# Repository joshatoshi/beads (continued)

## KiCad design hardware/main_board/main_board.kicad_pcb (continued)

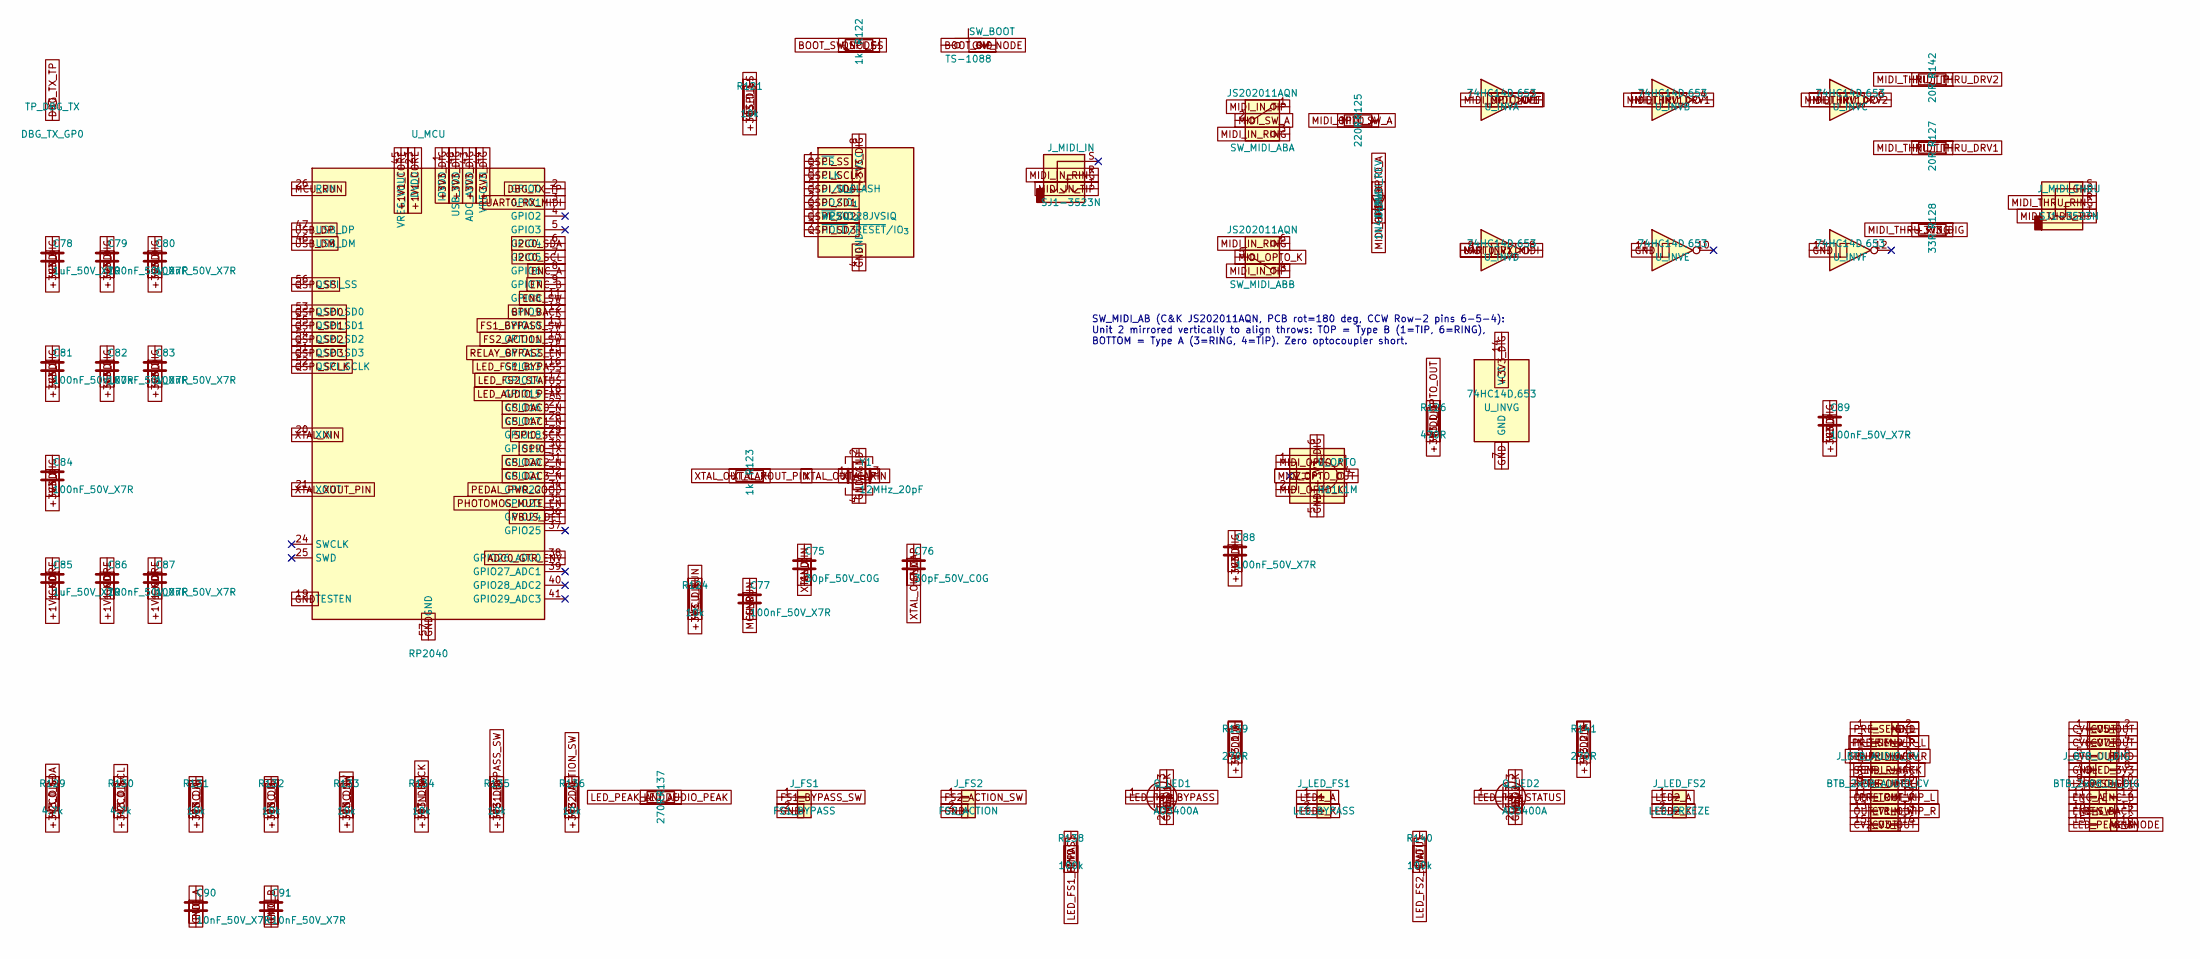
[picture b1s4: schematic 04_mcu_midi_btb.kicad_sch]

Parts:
C75, C76: 30pF_50V_C0G; C_0603_1608Metric
C77, C79, C80, C81, C82, C83, C84, C86, C87, C88, C89: 100nF_50V_X7R; C_0603_1608Metric
C78, C85: 1uF_50V_X7R; C_0805_2012Metric
C90, C91: 10nF_50V_X7R; C_0603_1608Metric
D_MIDI_REV: 1N4148W; D_SOD-123
J_BTB_AUDIO_CV: BTB_2x08_AUDIO_CV; PinHeader_2x08_P2.54mm_Vertical
J_BTB_UI_DIG: BTB_2x08_UI_DIG; PinHeader_2x08_P2.54mm_Vertical
J_FS1: FS1_BYPASS; PinHeader_1x02_P2.54mm_Vertical
J_FS2: FS2_ACTION; PinHeader_1x02_P2.54mm_Vertical
J_LED_FS1: LED_BYPASS; PinHeader_1x02_P2.54mm_Vertical
J_LED_FS2: LED_FREEZE; PinHeader_1x02_P2.54mm_Vertical
J_MIDI_IN: SJ1-3523N; Jack_3.5mm_CUI_SJ1-3523N_Clean
J_MIDI_THRU: SJ1-3523N; Jack_3.5mm_CUI_SJ1-3523N_Clean
Q_LED1, Q_LED2: AO3400A; SOT-23
R121, R124, R131, R132, R133, R134, R135, R136: 10k; R_0603_1608Metric
R122, R123: 1k; R_0603_1608Metric
R125: 220R; R_0603_1608Metric
R126: 470R; R_0603_1608Metric
R127, R142: 20R; R_0603_1608Metric
R128: 33R; R_0603_1608Metric
R129, R130: 4.7k; R_0603_1608Metric
R137, R139, R141: 270R; R_0603_1608Metric
R138, R140: 100k; R_0603_1608Metric
SW_BOOT: TS-1088; SW_Push_TS-1088_4.0x3.0mm
SW_MIDI_AB: JS202011AQN; SW_CK_JS202011AQN_DPDT_Angled
TP_DBG_TX: DBG_TX_GP0; TestPoint_Pad_D1.0mm
U_FLASH: W25Q128JVSIQ; SOIC-8_5.3x5.3mm_P1.27mm
U_INV: 74HC14D,653; SOIC-14_3.9x8.7mm_P1.27mm
U_MCU: RP2040; QFN-56-1EP_7x7mm_RP2040_SegPaste
U_OPTO: H11L1M; DIP-6_W7.62mm
Y1: 12MHz_20pF; Crystal_SMD_3225-4Pin_3.2x2.5mm

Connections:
+1V1_CORE: C85.1, C86.1, C87.1, U_MCU.23 (DVDD), U_MCU.45 (VREG_VOUT), U_MCU.50 (DVDD)
+3V3_DIG: C78.1, C79.1, C80.1, C81.1, C82.1, C83.1, C84.1, C88.1, C89.1, R121.1, R124.1, R126.1, R128.1, R129.1, R130.1, R131.1, R132.1, R133.1, R134.1, R135.1, R136.1, R139.1, R141.1, U_FLASH.8 (VCC), U_INV.14 (VCC), U_MCU.1 (IOVDD), U_MCU.10 (IOVDD), U_MCU.22 (IOVDD), U_MCU.33 (IOVDD), U_MCU.42 (IOVDD), U_MCU.43 (ADC_AVDD), U_MCU.44 (VREG_IN), U_MCU.48 (USB_VDD), U_MCU.49 (IOVDD), U_OPTO.6; also elsewhere on the board
ADC0_GTR_ENV: U_MCU.38 (GPIO26_ADC0); also elsewhere on the board
BOOT_SW_NODE: R122.2, SW_BOOT.1
BTN_BACK: J_BTB_UI_DIG.14, R134.2, U_MCU.12 (GPIO9)
CS_DAC0_N: U_MCU.27 (GPIO16); also elsewhere on the board
CS_DAC1_N: U_MCU.28 (GPIO17); also elsewhere on the board
CS_DAC2_N: U_MCU.31 (GPIO20); also elsewhere on the board
CS_DAC3_N: U_MCU.32 (GPIO21); also elsewhere on the board
CV1_OUT: J_BTB_AUDIO_CV.14; also elsewhere on the board
CV2_OUT: J_BTB_AUDIO_CV.15; also elsewhere on the board
CV3_OUT: J_BTB_AUDIO_CV.16; also elsewhere on the board
CV4_OUT: J_BTB_UI_DIG.1; also elsewhere on the board
CV5_OUT: J_BTB_UI_DIG.2; also elsewhere on the board
CV6_OUT: J_BTB_UI_DIG.3; also elsewhere on the board
CV7_OUT: J_BTB_UI_DIG.4; also elsewhere on the board
CV8_OUT: J_BTB_UI_DIG.5; also elsewhere on the board
DBG_TX_TP: TP_DBG_TX.1, U_MCU.2 (GPIO0)
ENC_A: C90.1, J_BTB_UI_DIG.11, R131.2, U_MCU.8 (GPIO6)
ENC_B: C91.1, J_BTB_UI_DIG.12, R132.2, U_MCU.9 (GPIO7)
ENC_SW: J_BTB_UI_DIG.13, R133.2, U_MCU.11 (GPIO8)
FS1_BYPASS_SW: J_FS1.1, R135.2, U_MCU.13 (GPIO10)
FS2_ACTION_SW: J_FS2.1, R136.2, U_MCU.14 (GPIO11)
GND: C75.2, C76.2, C77.2, C78.2, C79.2, C80.2, C81.2, C82.2, C83.2, C84.2, C85.2, C86.2, C87.2, C88.2, C89.2, C90.2, C91.2, J_BTB_AUDIO_CV.2, J_BTB_UI_DIG.6, J_BTB_UI_DIG.7, J_BTB_UI_DIG.16, J_FS1.2, J_FS2.2, J_MIDI_THRU.S, Q_LED1.2 (S), Q_LED2.2 (S), R138.2, R140.2, SW_BOOT.2, U_FLASH.4 (GND), U_INV.7 (GND), U_INV.11, U_INV.13, U_MCU.19 (TESTEN), U_MCU.57 (GND), U_OPTO.5, Y1.2, Y1.4; also elsewhere on the board
I2C0_SCL: J_BTB_UI_DIG.10, R130.2, U_MCU.7 (GPIO5)
I2C0_SDA: J_BTB_UI_DIG.9, R129.2, U_MCU.6 (GPIO4)
IN_TRIM_WIP_L: J_BTB_AUDIO_CV.3; also elsewhere on the board
IN_TRIM_WIP_R: J_BTB_AUDIO_CV.5; also elsewhere on the board
LED1_A: J_LED_FS1.1, R139.2
LED1_K: J_LED_FS1.2, Q_LED1.3 (D)
LED2_A: J_LED_FS2.1, R141.2
LED2_K: J_LED_FS2.2, Q_LED2.3 (D)
LED_AUDIO_PEAK: R137.1, U_MCU.18 (GPIO15)
LED_FS1_BYPASS: Q_LED1.1 (G), R138.1, U_MCU.16 (GPIO13)
LED_FS2_STATUS: Q_LED2.1 (G), R140.1, U_MCU.17 (GPIO14)
LED_PEAK_ANODE: J_BTB_UI_DIG.15, R137.2
MCU_RUN: C77.1, R124.2, U_MCU.26 (RUN)
MIDI_INV1: U_INV.2, U_INV.3, U_INV.5, U_INV.9
MIDI_IN_RING: J_MIDI_IN.R, SW_MIDI_AB.3 (C), SW_MIDI_AB.6 (C)
MIDI_IN_TIP: J_MIDI_IN.T, SW_MIDI_AB.1 (A), SW_MIDI_AB.4 (A)
MIDI_OPTO_A: D_MIDI_REV.1 (K), R125.2, U_OPTO.1
MIDI_OPTO_K: D_MIDI_REV.2 (A), SW_MIDI_AB.5 (B), U_OPTO.2
MIDI_OPTO_OUT: R126.2, U_INV.1, U_OPTO.4
MIDI_SW_A: R125.1, SW_MIDI_AB.2 (B)
MIDI_THRU_DRV1: R127.1, U_INV.4
MIDI_THRU_DRV2: R142.1, U_INV.6
MIDI_THRU_RING: J_MIDI_THRU.R, R128.2
MIDI_THRU_TIP: J_MIDI_THRU.T, R127.2, R142.2
OLED_3V3: J_BTB_UI_DIG.8; also elsewhere on the board
OUT_TRIM_WIP_L: J_BTB_AUDIO_CV.11; also elsewhere on the board
OUT_TRIM_WIP_R: J_BTB_AUDIO_CV.13; also elsewhere on the board
PEDAL_PWR_GOOD: U_MCU.34 (GPIO22); also elsewhere on the board
PHOTOMOS_MUTE_EN: U_MCU.35 (GPIO23); also elsewhere on the board
PRE_OUT_L: J_BTB_AUDIO_CV.10; also elsewhere on the board
PRE_OUT_R: J_BTB_AUDIO_CV.12; also elsewhere on the board
PRE_SEND_L: J_BTB_AUDIO_CV.1; also elsewhere on the board
PRE_SEND_R: J_BTB_AUDIO_CV.4; also elsewhere on the board
QSPI_SCLK: U_FLASH.6 (CLK), U_MCU.52 (QSPI_SCLK)
QSPI_SD0: U_FLASH.5 (DI/IO_{0}), U_MCU.53 (QSPI_SD0)
QSPI_SD1: U_FLASH.2 (DO/IO_{1}), U_MCU.55 (QSPI_SD1)
QSPI_SD2: U_FLASH.3 (~WP/IO_{2}), U_MCU.54 (QSPI_SD2)
QSPI_SD3: U_FLASH.7 (~HOLD/~RESET/IO_{3}), U_MCU.51 (QSPI_SD3)
QSPI_SS: R121.2, R122.1, U_FLASH.1 (~CS), U_MCU.56 (QSPI_SS)
RELAY_BYPASS_EN: U_MCU.15 (GPIO12); also elsewhere on the board
RET_L_JACK: J_BTB_AUDIO_CV.8; also elsewhere on the board
RET_R_JACK: J_BTB_AUDIO_CV.9; also elsewhere on the board
SEND_L_JACK: J_BTB_AUDIO_CV.6; also elsewhere on the board
SEND_R_JACK: J_BTB_AUDIO_CV.7; also elsewhere on the board
SPI0_SCK: U_MCU.29 (GPIO18); also elsewhere on the board
SPI0_TX: U_MCU.30 (GPIO19); also elsewhere on the board
UART0_RX_MIDI: U_INV.8, U_MCU.3 (GPIO1)
USB_DM: U_MCU.46 (USB_DM); also elsewhere on the board
USB_DP: U_MCU.47 (USB_DP); also elsewhere on the board
VBUS_DET: U_MCU.36 (GPIO24); also elsewhere on the board
XTAL_OUT_CAP: C76.1, R123.2, Y1.3
XTAL_XIN: C75.1, U_MCU.20 (XIN), Y1.1
XTAL_XOUT_PIN: R123.1, U_MCU.21 (XOUT)

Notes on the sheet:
SW_MIDI_AB (C&K JS202011AQN, PCB rot=180 deg, CCW Row-2 pins 6-5-4): Unit 2 mirrored vertically to align throws: TOP = Type B (1=TIP, 6=RING), BOTTOM = Type A (3=RING, 4=TIP). Zero optocoupler short.

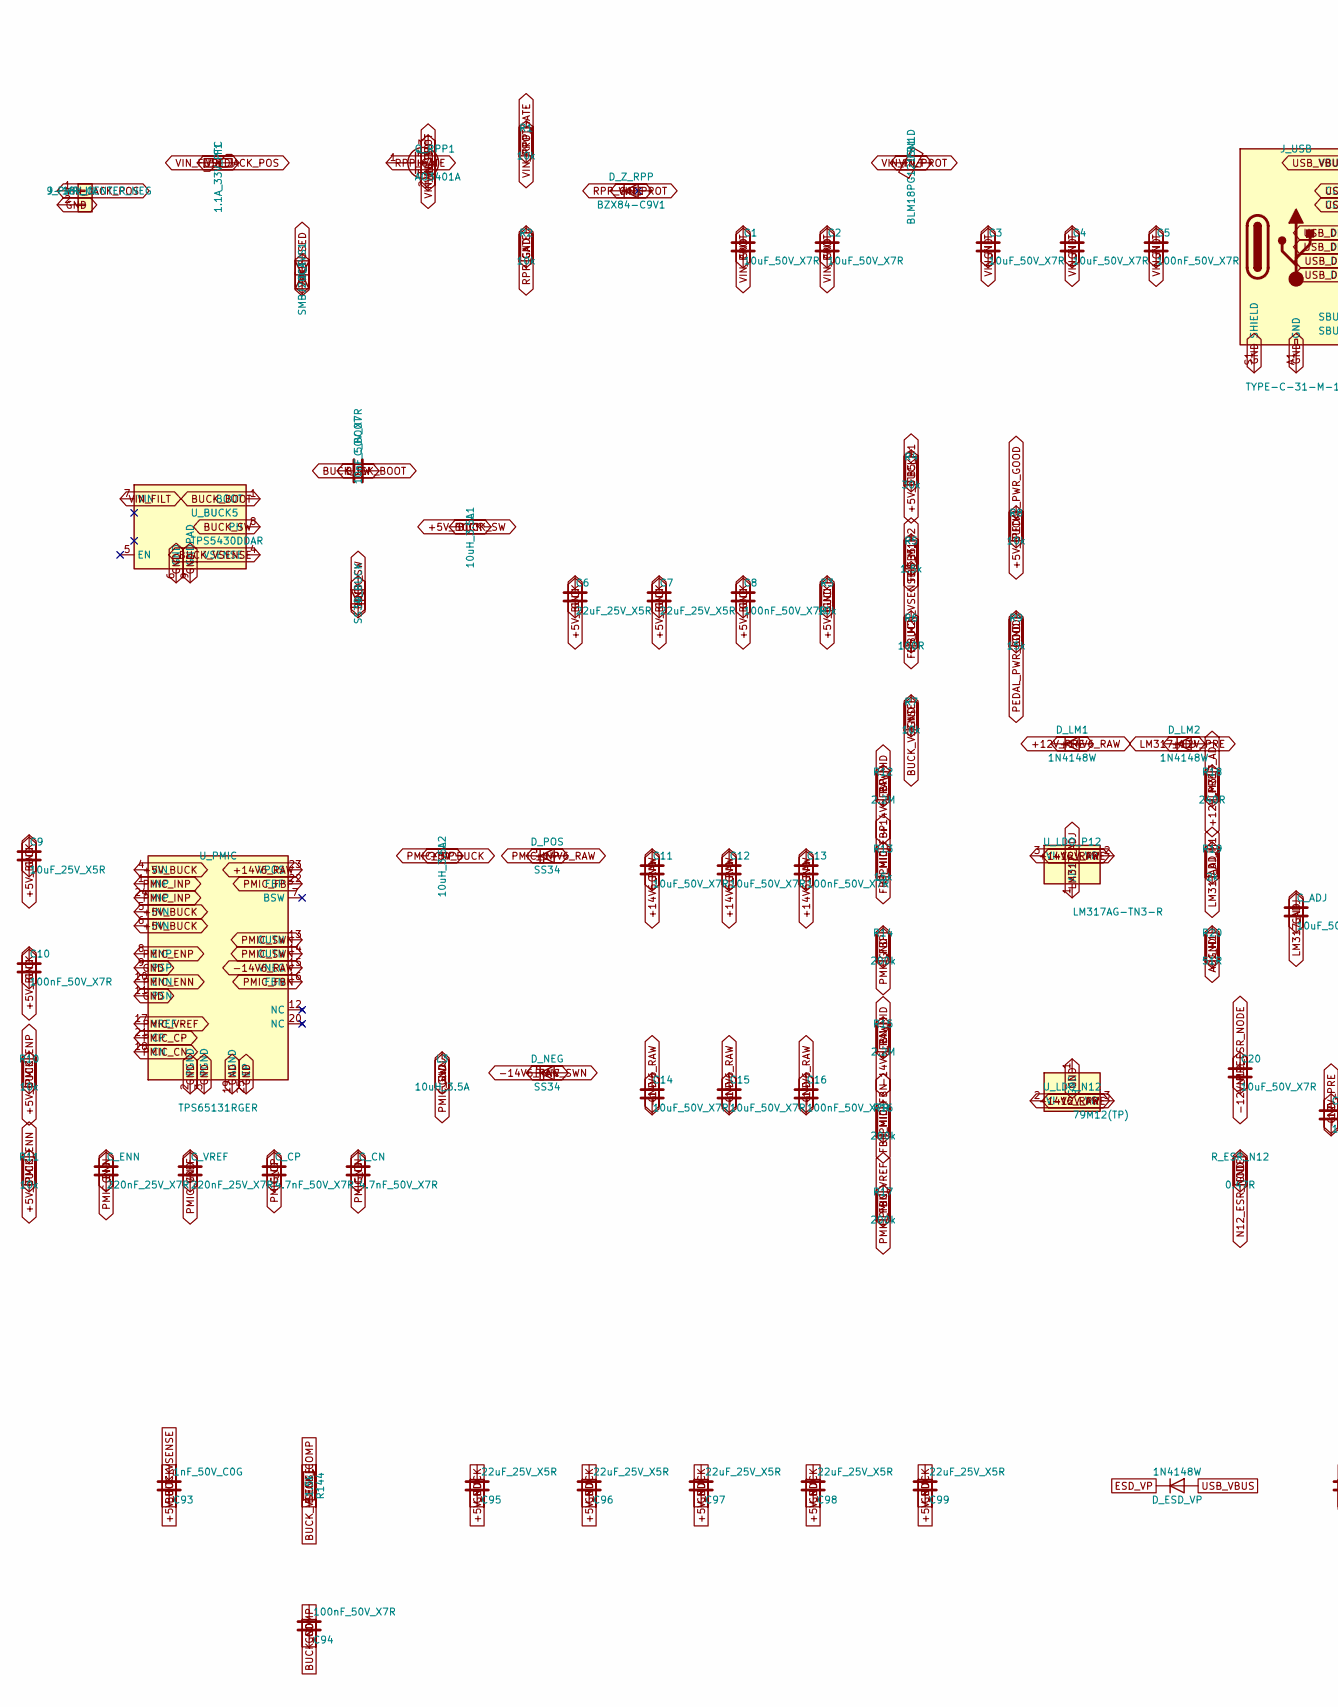
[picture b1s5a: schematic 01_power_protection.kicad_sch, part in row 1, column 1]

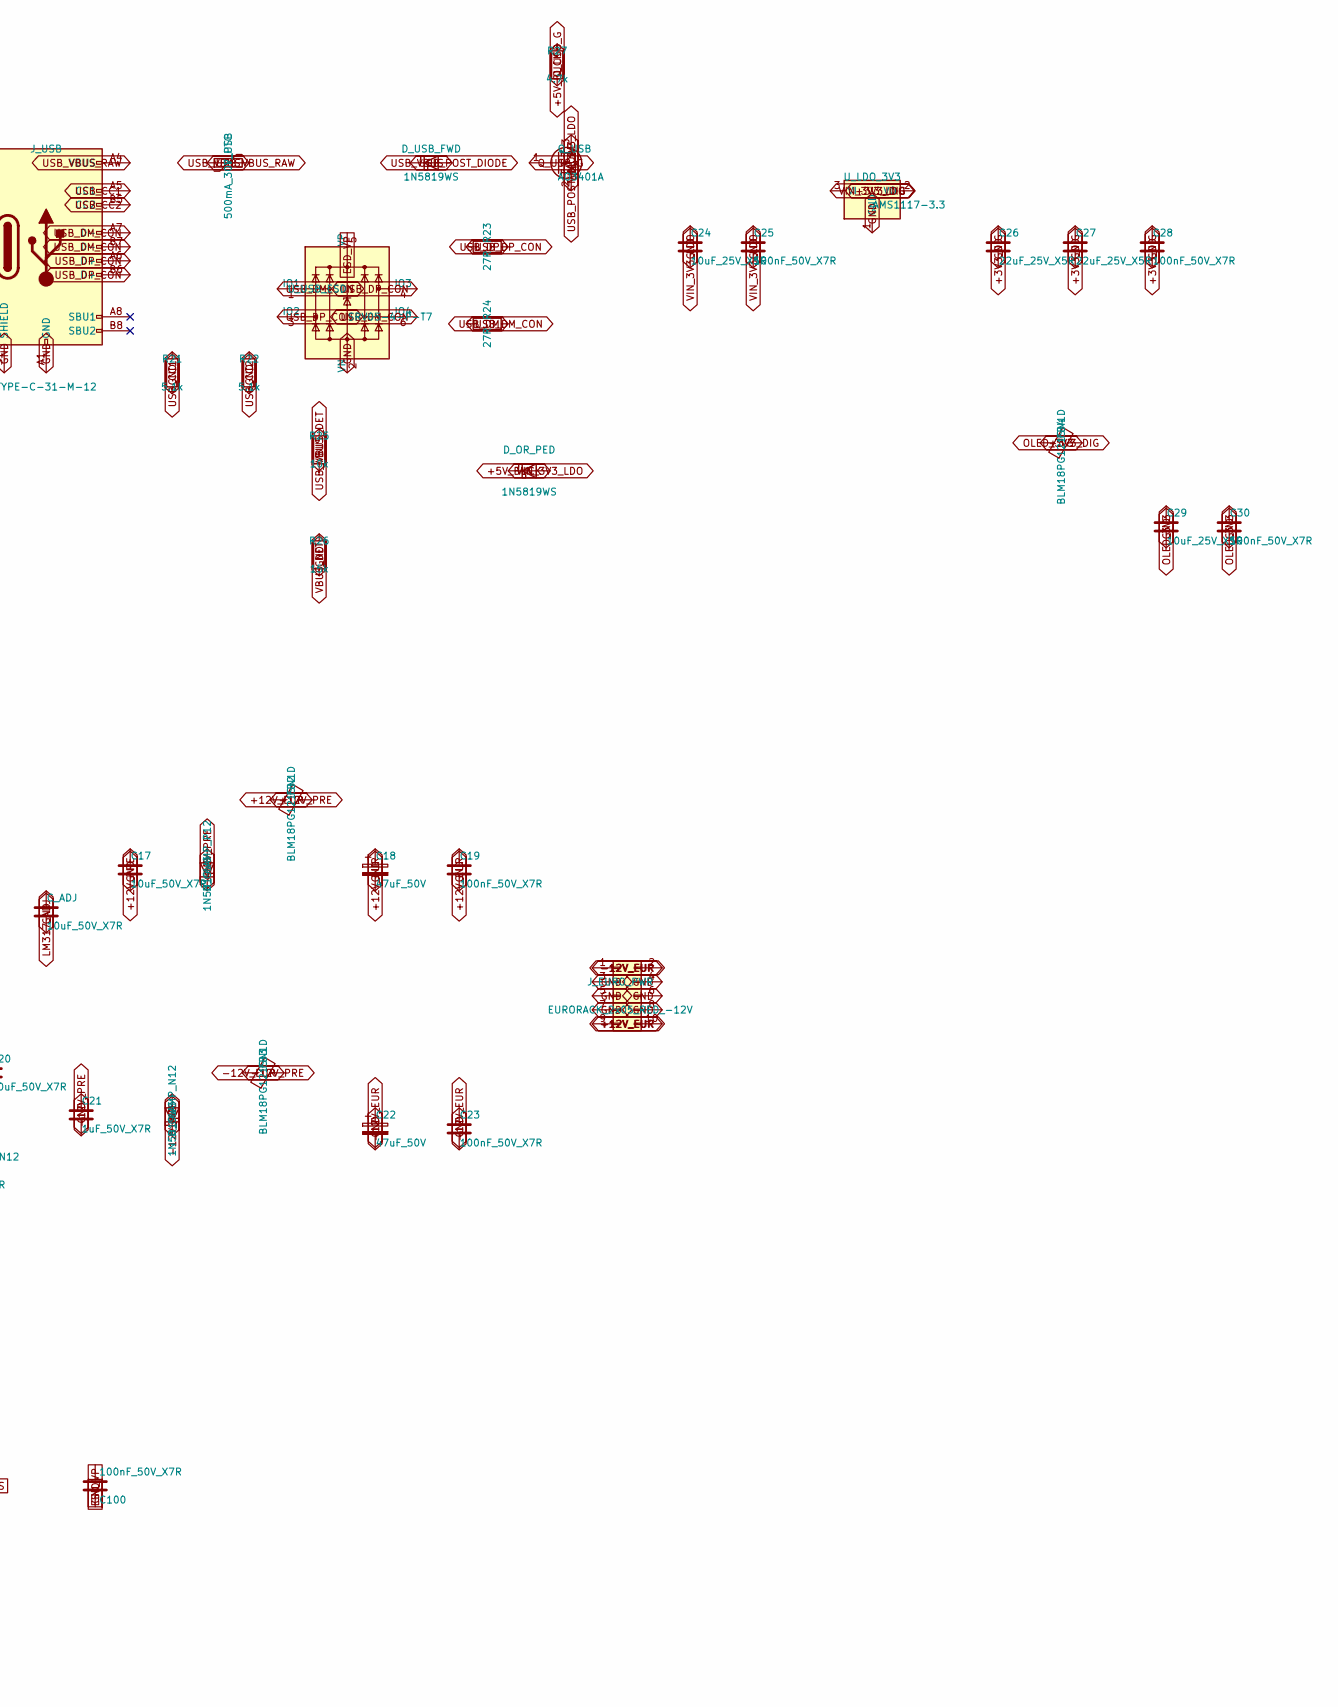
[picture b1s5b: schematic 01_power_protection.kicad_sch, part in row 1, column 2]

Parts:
C1, C2, C3, C4, C11, C12, C14, C15, C17, C20: 10uF_50V_X7R; C_1206_3216Metric
C5, C8, C10, C13, C16, C19, C23, C25, C28, C30, C94, C100: 100nF_50V_X7R; C_0603_1608Metric
C6, C7, C26, C27, C95, C96, C97, C98, C99: 22uF_25V_X5R; C_1206_3216Metric
C9, C24, C29: 10uF_25V_X5R; C_0805_2012Metric
C18, C22: 47uF_50V; CP_Elec_6.3x7.7
C21: 1uF_50V_X7R; C_0805_2012Metric
C93: 1nF_50V_C0G; C_0603_1608Metric
C_ADJ: 10uF_50V_X7R; C_1206_3216Metric
C_BOOT: 10nF_50V_X7R; C_0603_1608Metric
C_CN: 4.7nF_50V_X7R; C_0603_1608Metric
C_CP: 4.7nF_50V_X7R; C_0603_1608Metric
C_ENN: 220nF_25V_X7R; C_0603_1608Metric
C_VREF: 220nF_25V_X7R; C_0603_1608Metric
D_BUCK: SS34; D_SMA
D_CLAMP_N12: 1N5819WS; D_SOD-323
D_CLAMP_P12: 1N5819WS; D_SOD-323
D_ESD_VP: 1N4148W; D_SOD-123
D_LM1, D_LM2: 1N4148W; D_SOD-123
D_NEG: SS34; D_SMA
D_OR_PED: 1N5819WS; D_SOD-323
D_POS: SS34; D_SMA
D_TVS1: SMBJ20CA; D_SMB
D_USB_FWD: 1N5819WS; D_SOD-323
D_Z_RPP: BZX84-C9V1; SOT-23
F1: 1.1A_33V_PTC; Fuse_1812_4532Metric
FB1, FB2, FB3, FB4: BLM18PG121SN1D; L_0603_1608Metric
F_USB: 500mA_30V_PTC; Fuse_1206_3216Metric
J_EURO_PWR: EURORACK_2x05_RED_-12V; IDC-Header_2x05_P2.54mm_Vertical
J_PWR_IN: 9-18V_CENTER_NEG; PinHeader_1x02_P2.54mm_Vertical
J_USB: TYPE-C-31-M-12; USB_C_Receptacle_HRO_TYPE-C-31-M-12_EdgeClean
L1, L2, L3: 10uH_3.5A; L_APV_APH0530
Q_RPP1: AO3401A; SOT-23
Q_USB: AO3401A; SOT-23
R1, R2, R3, R7, R8, R10, R11, R25: 10k; R_0603_1608Metric
R4: 30k; R_0603_1608Metric
R5, R144: 1.5k; R_0603_1608Metric
R6: 100R; R_0603_1608Metric
R9, R13, R26: 15k; R_0603_1608Metric
R12, R15: 2.2M; R_0603_1608Metric
R14, R16, R17: 200k; R_0603_1608Metric
R18: 240R; R_0603_1608Metric
R19: 2k; R_0603_1608Metric
R20: 51R; R_0603_1608Metric
R21, R22: 5.1k; R_0603_1608Metric
R23, R24: 27R; R_0603_1608Metric
R27: 4.7k; R_0603_1608Metric
R_ESR_N12: 0.47R; R_0805_2012Metric
U_BUCK5: TPS5430DDAR; SOIC-8-1EP_TPS5430_SegPaste
U_LDO_3V3: AMS1117-3.3; SOT-223-3_TabPin2
U_LDO_N12: 79M12(TP); TO-252-2
U_LDO_P12: LM317AG-TN3-R; TO-252-2
U_PMIC: TPS65131RGER; VQFN-24-1EP_4x4mm_TPS65131_SegPaste
U_USB_ESD: SRV05-4-P-T7; SOT-23-6

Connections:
+3V3_DIG: C26.1, C27.1, C28.1, FB4.1, U_LDO_3V3.2 (VO); also elsewhere on the board
+5V_BUCK: C6.1, C7.1, C8.1, C9.1, C10.1, C93.1, C95.1, C96.1, C97.1, C98.1, C99.1, D_OR_PED.2 (A), L1.2, L2.1, R3.1, R4.1, R8.1, R10.1, R11.1, R27.1, U_PMIC.4 (VIN), U_PMIC.5 (INN), U_PMIC.6 (INN); also elsewhere on the board
+12V_EUR: C18.1, C19.1, FB2.2, J_EURO_PWR.9, J_EURO_PWR.10; also elsewhere on the board
+12V_PRE: C17.1, D_CLAMP_P12.1 (K), D_LM1.2 (A), D_LM2.1 (K), FB2.1, R18.1, U_LDO_P12.2 (VO)
+14V6_RAW: C11.1, C12.1, C13.1, D_LM1.1 (K), D_POS.1 (K), R12.1, U_LDO_P12.3 (VI), U_PMIC.23 (VPOS)
-12V_EUR: C22.2, C23.2, FB3.2, J_EURO_PWR.1, J_EURO_PWR.2; also elsewhere on the board
-12V_PRE: C20.1, C21.2, D_CLAMP_N12.2 (A), FB3.1, U_LDO_N12.3 (VO)
-14V6_RAW: C14.2, C15.2, C16.2, D_NEG.2 (A), R15.1, U_LDO_N12.2 (VI), U_PMIC.15 (VNEG)
ADJ_M1: R19.2, R20.1
BUCK_BOOT: C_BOOT.1, U_BUCK5.1 (BOOT)
BUCK_COMP: C94.1, R144.2
BUCK_SW: C_BOOT.2, D_BUCK.1 (K), L1.1, U_BUCK5.8 (PH)
BUCK_VSENSE: C93.2, R6.2, R7.1, R144.1, U_BUCK5.4 (VSENSE)
ESD_VP: C100.1, D_ESD_VP.1 (K), U_USB_ESD.5 (VP)
FB5_M1: R4.2, R5.1
FB5_M2: R5.2, R6.1
FBN_MID: R15.2, R16.1
FBP_MID: R12.2, R13.1
GND: C1.2, C2.2, C3.2, C4.2, C5.2, C6.2, C7.2, C8.2, C9.2, C10.2, C11.2, C12.2, C13.2, C14.1, C15.1, C16.1, C17.2, C18.2, C19.2, C21.1, C22.1, C23.1, C24.2, C25.2, C26.2, C27.2, C28.2, C29.2, C30.2, C94.2, C95.2, C96.2, C97.2, C98.2, C99.2, C100.2, C_ADJ.2, C_CN.2, C_CP.2, C_ENN.2, C_VREF.2, D_BUCK.2 (A), D_CLAMP_N12.1 (K), D_CLAMP_P12.2 (A), D_TVS1.2 (A2), J_EURO_PWR.3, J_EURO_PWR.4, J_EURO_PWR.5, J_EURO_PWR.6, J_EURO_PWR.7, J_EURO_PWR.8, J_PWR_IN.2, J_USB.A1 (GND), J_USB.A12 (GND), J_USB.B1 (GND), J_USB.B12 (GND), J_USB.S1 (SHIELD), L3.2, R2.2, R3.2, R7.2, R9.2, R14.2, R20.2, R21.2, R22.2, R26.2, R_ESR_N12.2, U_BUCK5.6 (GND), U_BUCK5.9 (GNDPAD), U_LDO_3V3.1 (GND), U_LDO_N12.1 (GND), U_PMIC.2 (PGND), U_PMIC.3 (PGND), U_PMIC.9 (PSP), U_PMIC.11 (PSN), U_PMIC.19 (AGND), U_PMIC.25 (EP), U_USB_ESD.2 (VN); also elsewhere on the board
LM317_ADJ: C_ADJ.1, D_LM2.2 (A), R18.2, R19.1, U_LDO_P12.1 (ADJ)
N12_ESR_NODE: C20.2, R_ESR_N12.1
OLED_3V3: C29.1, C30.1, FB4.2; also elsewhere on the board
PEDAL_PWR_GOOD: R8.2, R9.1; also elsewhere on the board
PMIC_CN: C_CN.1, U_PMIC.18 (CN)
PMIC_CP: C_CP.1, U_PMIC.21 (CP)
PMIC_ENN: C_ENN.1, R11.2, U_PMIC.10 (ENN)
PMIC_ENP: R10.2, U_PMIC.8 (ENP)
PMIC_FBN: R16.2, R17.1, U_PMIC.16 (FBN)
PMIC_FBP: R13.2, R14.1, U_PMIC.22 (FBP)
PMIC_INP: D_POS.2 (A), L2.2, U_PMIC.1 (INP), U_PMIC.24 (INP)
PMIC_SWN: D_NEG.1 (K), L3.1, U_PMIC.13 (OUTN), U_PMIC.14 (OUTN)
PMIC_VREF: C_VREF.1, R17.2, U_PMIC.17 (VREF)
Q_USB_G: Q_USB.1 (G), R27.2
RPP_GATE: D_Z_RPP.1 (A), Q_RPP1.1 (G), R1.2, R2.1
USB_CC1: J_USB.A5 (CC1), R21.1
USB_CC2: J_USB.B5 (CC2), R22.1
USB_DM: R24.2; also elsewhere on the board
USB_DM_CON: J_USB.A7 (D-), J_USB.B7 (D-), R24.1, U_USB_ESD.1 (IO1), U_USB_ESD.6 (IO4)
USB_DP: R23.2; also elsewhere on the board
USB_DP_CON: J_USB.A6 (D+), J_USB.B6 (D+), R23.1, U_USB_ESD.3 (IO2), U_USB_ESD.4 (IO3)
USB_POST_DIODE: D_USB_FWD.1 (K), Q_USB.3 (D)
USB_VBUS: D_ESD_VP.2 (A), D_USB_FWD.2 (A), F_USB.2, R25.1
USB_VBUS_RAW: F_USB.1, J_USB.A4 (VBUS), J_USB.A9 (VBUS), J_USB.B4 (VBUS), J_USB.B9 (VBUS)
VBUS_DET: R25.2, R26.1; also elsewhere on the board
VIN_3V3_LDO: C24.1, C25.1, D_OR_PED.1 (K), Q_USB.2 (S), U_LDO_3V3.3 (VI)
VIN_FILT: C3.1, C4.1, C5.1, FB1.2, U_BUCK5.7 (VIN)
VIN_FUSED: D_TVS1.1 (A1), F1.2, Q_RPP1.3 (D)
VIN_JACK_POS: F1.1, J_PWR_IN.1
VIN_PROT: C1.1, C2.1, D_Z_RPP.3 (K), FB1.1, Q_RPP1.2 (S), R1.1

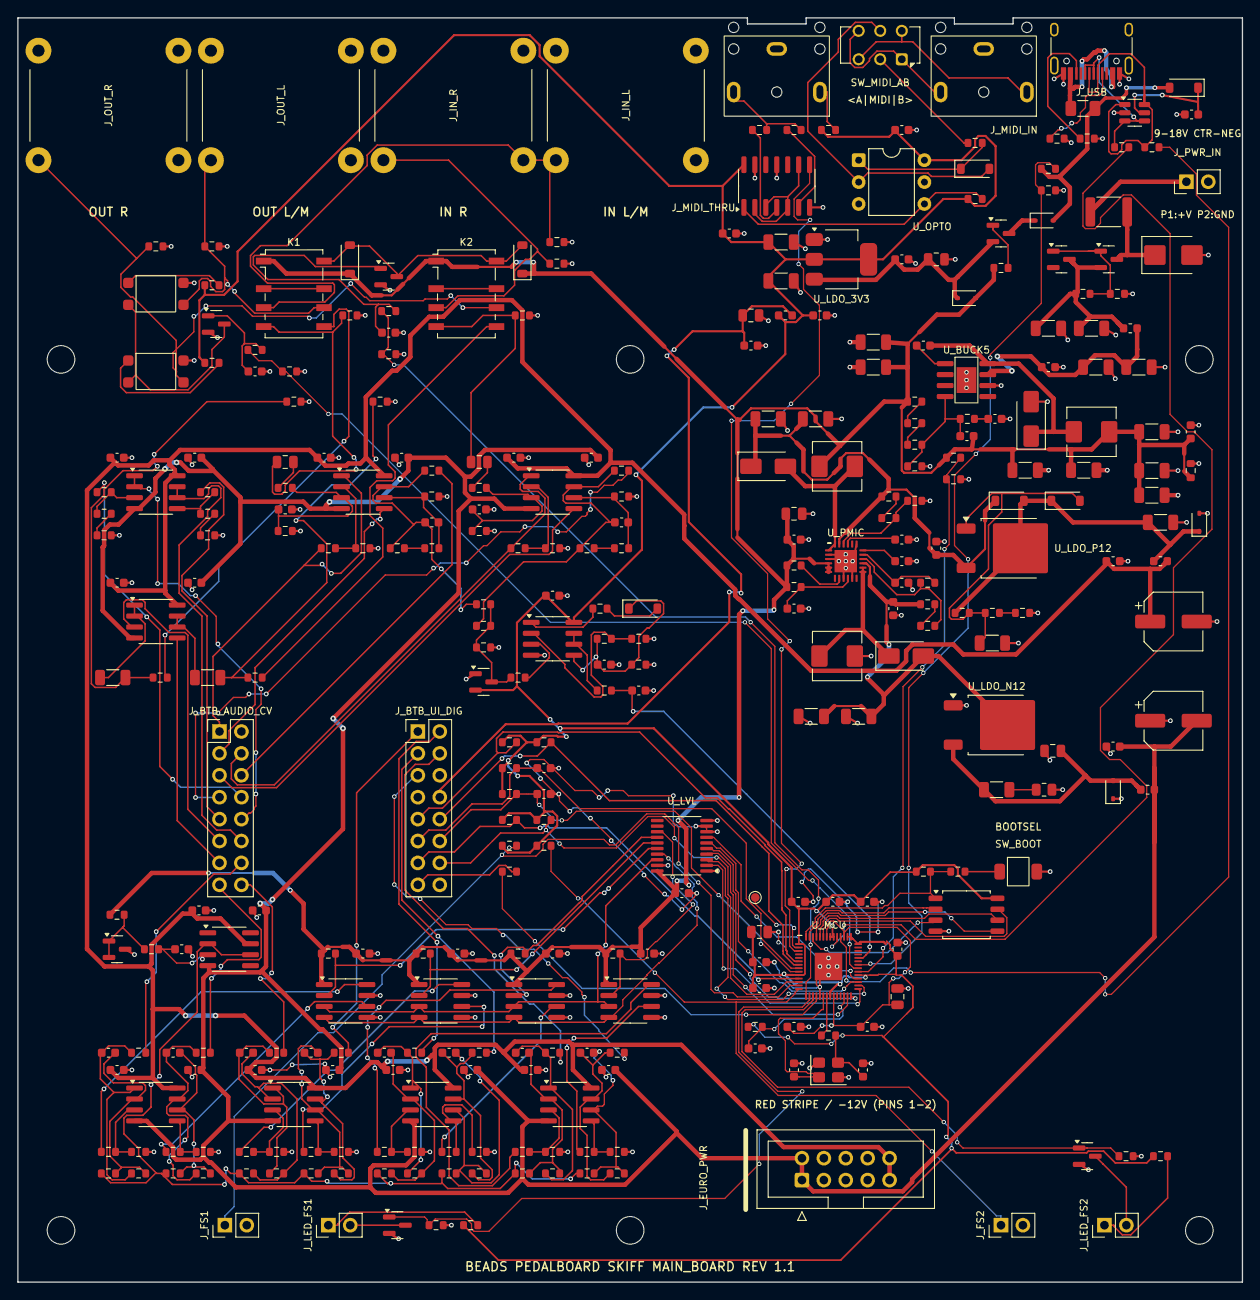
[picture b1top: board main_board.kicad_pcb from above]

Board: 2 copper layers, 142.0 x 146.6 mm, 337 parts (0 on the bottom side), 203 nets.

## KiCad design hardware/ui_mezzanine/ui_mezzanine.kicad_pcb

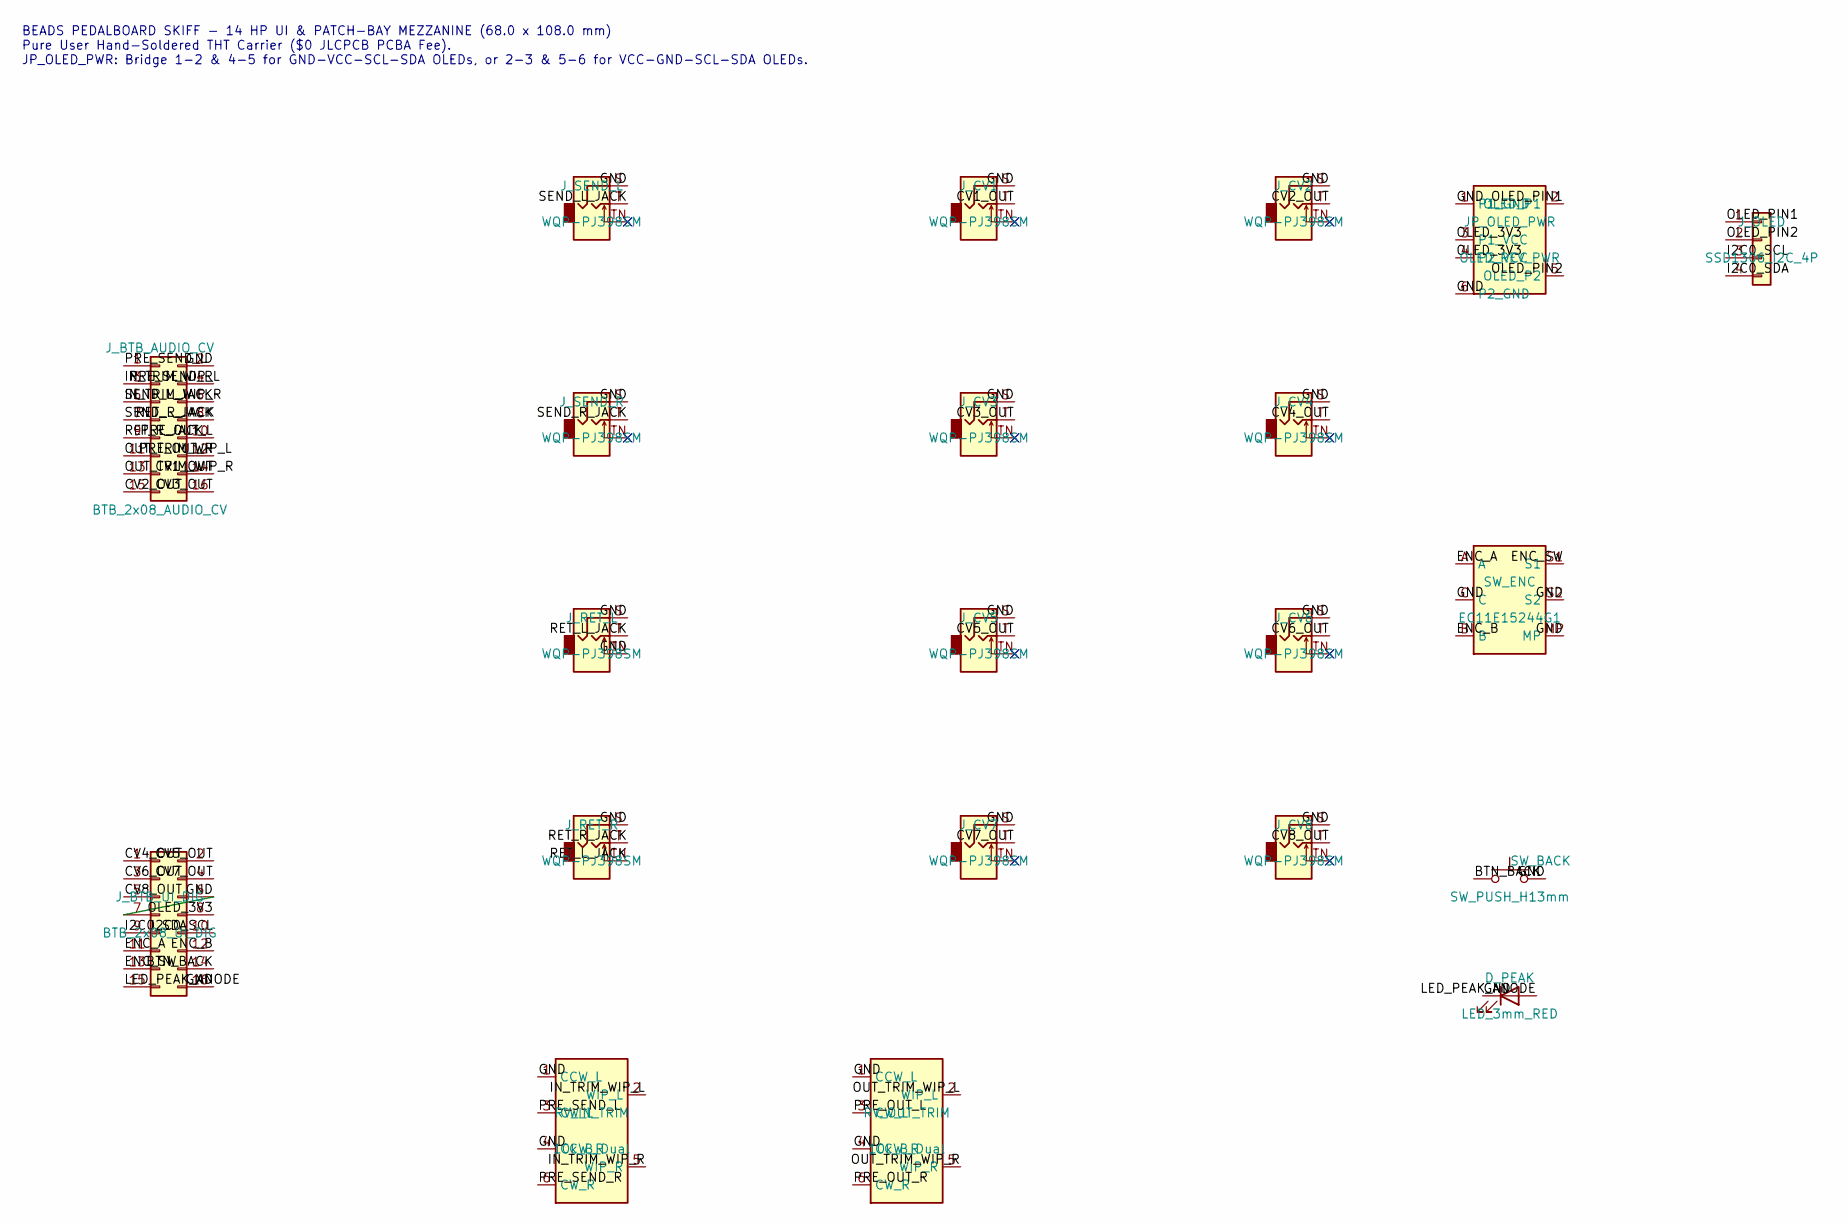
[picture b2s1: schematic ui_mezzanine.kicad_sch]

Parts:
D_PEAK: LED_3mm_RED; LED_D3.0mm
JP_OLED_PWR: OLED_REV_PWR; SolderJumper_OLED_RevPWR
J_BTB_AUDIO_CV: BTB_2x08_AUDIO_CV; BTB_Socket_2x08_P2.54mm_BottomMate
J_BTB_UI_DIG: BTB_2x08_UI_DIG; BTB_Socket_2x08_P2.54mm_BottomMate
J_CV1, J_CV2, J_CV3, J_CV4, J_CV5, J_CV6, J_CV7, J_CV8: WQP-PJ398SM; Jack_3.5mm_QingPu_WQP-PJ398SM_Vertical_CircularHoles
J_OLED: SSD1306_I2C_4P; PinSocket_1x04_P2.54mm_Vertical
J_RET_L: WQP-PJ398SM; Jack_3.5mm_QingPu_WQP-PJ398SM_Vertical_CircularHoles
J_RET_R: WQP-PJ398SM; Jack_3.5mm_QingPu_WQP-PJ398SM_Vertical_CircularHoles
J_SEND_L: WQP-PJ398SM; Jack_3.5mm_QingPu_WQP-PJ398SM_Vertical_CircularHoles
J_SEND_R: WQP-PJ398SM; Jack_3.5mm_QingPu_WQP-PJ398SM_Vertical_CircularHoles
RV_IN_TRIM: 10k_B_Dual; Potentiometer_Alpha_RD902F-40-00D_Dual_Vertical
RV_OUT_TRIM: 10k_B_Dual; Potentiometer_Alpha_RD902F-40-00D_Dual_Vertical
SW_BACK: SW_PUSH_H13mm; SW_PUSH_6mm_H13mm
SW_ENC: EC11E15244G1; RotaryEncoder_Alps_EC11E-Switch_Vertical_H20mm_CircularMoun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

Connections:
BTN_BACK: J_BTB_UI_DIG.14, SW_BACK.1
CV1_OUT: J_BTB_AUDIO_CV.14, J_CV1.T
CV2_OUT: J_BTB_AUDIO_CV.15, J_CV2.T
CV3_OUT: J_BTB_AUDIO_CV.16, J_CV3.T
CV4_OUT: J_BTB_UI_DIG.1, J_CV4.T
CV5_OUT: J_BTB_UI_DIG.2, J_CV5.T
CV6_OUT: J_BTB_UI_DIG.3, J_CV6.T
CV7_OUT: J_BTB_UI_DIG.4, J_CV7.T
CV8_OUT: J_BTB_UI_DIG.5, J_CV8.T
ENC_A: J_BTB_UI_DIG.11, SW_ENC.A
ENC_B: J_BTB_UI_DIG.12, SW_ENC.B
ENC_SW: J_BTB_UI_DIG.13, SW_ENC.S1
GND: D_PEAK.1 (K), JP_OLED_PWR.1 (P1_GND), JP_OLED_PWR.6 (P2_GND), J_BTB_AUDIO_CV.2, J_BTB_UI_DIG.6, J_BTB_UI_DIG.7, J_BTB_UI_DIG.16, J_CV1.S, J_CV2.S, J_CV3.S, J_CV4.S, J_CV5.S, J_CV6.S, J_CV7.S, J_CV8.S, J_RET_L.S, J_RET_L.TN, J_RET_R.S, J_SEND_L.S, J_SEND_R.S, RV_IN_TRIM.1 (CCW_L), RV_IN_TRIM.4 (CCW_R), RV_OUT_TRIM.1 (CCW_L), RV_OUT_TRIM.4 (CCW_R), SW_BACK.2, SW_ENC.C, SW_ENC.MP, SW_ENC.S2
I2C0_SCL: J_BTB_UI_DIG.10, J_OLED.3
I2C0_SDA: J_BTB_UI_DIG.9, J_OLED.4
IN_TRIM_WIP_L: J_BTB_AUDIO_CV.3, RV_IN_TRIM.2 (WIP_L)
IN_TRIM_WIP_R: J_BTB_AUDIO_CV.5, RV_IN_TRIM.5 (WIP_R)
LED_PEAK_ANODE: D_PEAK.2 (A), J_BTB_UI_DIG.15
OLED_3V3: JP_OLED_PWR.3 (P1_VCC), JP_OLED_PWR.4 (P2_VCC), J_BTB_UI_DIG.8
OLED_PIN1: JP_OLED_PWR.2 (OLED_P1), J_OLED.1
OLED_PIN2: JP_OLED_PWR.5 (OLED_P2), J_OLED.2
OUT_TRIM_WIP_L: J_BTB_AUDIO_CV.11, RV_OUT_TRIM.2 (WIP_L)
OUT_TRIM_WIP_R: J_BTB_AUDIO_CV.13, RV_OUT_TRIM.5 (WIP_R)
PRE_OUT_L: J_BTB_AUDIO_CV.10, RV_OUT_TRIM.3 (CW_L)
PRE_OUT_R: J_BTB_AUDIO_CV.12, RV_OUT_TRIM.6 (CW_R)
PRE_SEND_L: J_BTB_AUDIO_CV.1, RV_IN_TRIM.3 (CW_L)
PRE_SEND_R: J_BTB_AUDIO_CV.4, RV_IN_TRIM.6 (CW_R)
RET_L_JACK: J_BTB_AUDIO_CV.8, J_RET_L.T, J_RET_R.TN
RET_R_JACK: J_BTB_AUDIO_CV.9, J_RET_R.T
SEND_L_JACK: J_BTB_AUDIO_CV.6, J_SEND_L.T
SEND_R_JACK: J_BTB_AUDIO_CV.7, J_SEND_R.T

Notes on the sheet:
BEADS PEDALBOARD SKIFF - 14 HP UI & PATCH-BAY MEZZANINE (68.0 x 108.0 mm) Pure User Hand-Soldered THT Carrier ($0 JLCPCB PCBA Fee). JP_OLED_PWR: Bridge 1-2 & 4-5 for GND-VCC-SCL-SDA OLEDs, or 2-3 & 5-6 for VCC-GND-SCL-SDA OLEDs.

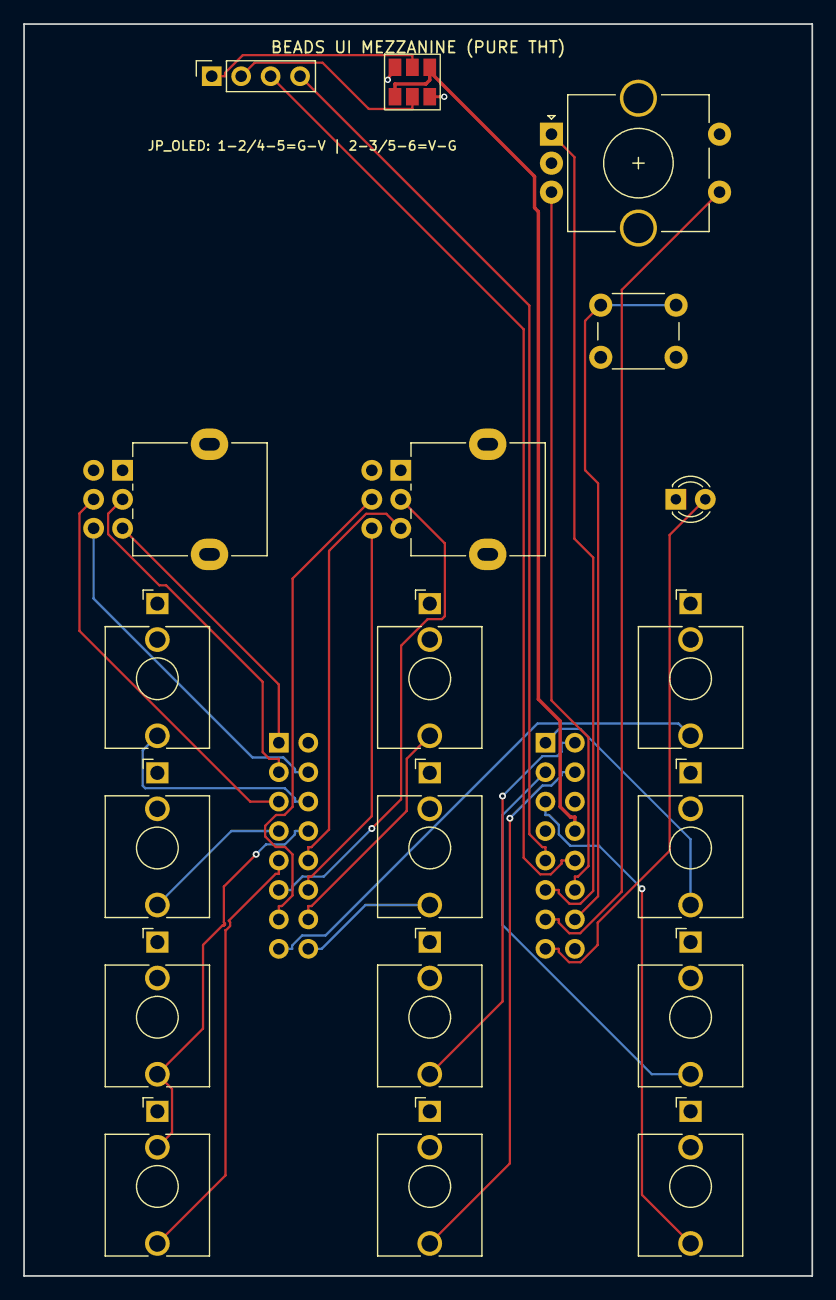
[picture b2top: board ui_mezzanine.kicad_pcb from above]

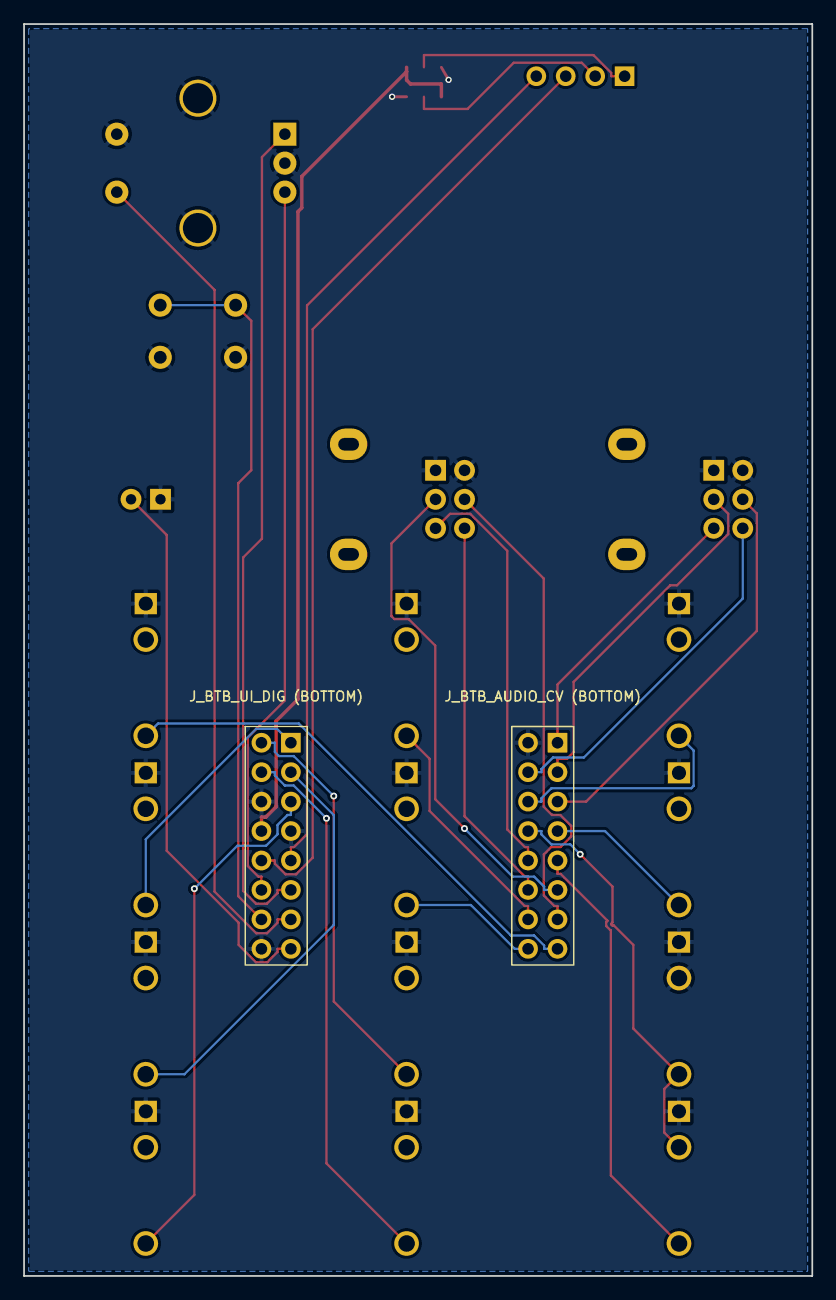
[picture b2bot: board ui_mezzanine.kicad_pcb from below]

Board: 2 copper layers, 68.0 x 108.0 mm, 21 parts (2 on the bottom side), 31 nets.
